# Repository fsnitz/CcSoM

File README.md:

# CcSoM

## Description
CcSoM is a credit card-sized System on Module built around the GateMate FPGA from Cologne Chip. It is designed to accommodate the CCGM1A1 and CCGM1A2 FPGAs with all their features. 
This repository contains all the necessary design files to fabricate and further develop the SoM itself or an application specific baseboard for it. 
A simple IO tester and programmer baseboard can be found in the [Baseboards](Baseboards) folder.
The [Library](Library) folder contains a symbol and footprint to simplify the process of creating a new baseboard. 
Each board folder includes a PDF version of the board and schematics, as well as an interactive HTML BOM.

## Features: 
  - Choose the IO-Bank supply voltage for each IO-Bank freely within the capability of the GateMate FPGA (default 2.5V).
  - All IOs are routed to the SODIMM-connector and can be accessed either as single-ended signal or as differential pair with its designated partner IO.
  - Configuration of the FPGA is possible over JTAG or the on-board QSPI-Flash.

## Manufacturing notes
- The SoM is designed for JLCPCBs "JLC0610H-3313" layer stack and with vias in pads. If a different manufacturer is chosen, it is advisable to either reroute all differential lines or to find a manufacturer where the layer stack can be specified.
- Most of the resistors and capacitors have a 0201 footprint, which may complicate the manufacturing process. 

## Author
Felix Sebastian Nitz

## Acknowledgment
A special thanks to Cologne chip and its employees for their feedback on the design and FPGA samples.

## License
This project falls under the open hardware licence agreement.

## Project status
- SoM revision 1.0 is currently tested with the CCGM1A1 FPGA. Beginning of 2025 an evaluation of its capabilities with an CCGM1A2 will follow.
- A version of the SoM with a 0402 footprint can be found under its designated Tag [0402 Version](https://github.com/fsnitz/CcSoM/tree/VersionWith0402Components).

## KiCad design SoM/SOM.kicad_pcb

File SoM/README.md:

# CcSoM

## Description
CcSoM is a credit card-sized System on Module built around the GateMate FPGA from Cologne Chip. It is designed to accommodate the CCGM1A1 and CCGM1A2 FPGAs with all their features. 
This repository contains all the necessary design files to fabricate and further develop the SoM itself or an application specific baseboard for it. 
A simple IO tester and programmer baseboard can be found in the Baseboard subfolder.
The Library folder contains a symbol and footprint to simplify the process of creating a new baseboard. 
Each board folder includes a PDF version of the board and schematics, as well as an interactive HTML BOM.

## Features: 
  - Choose the IO-Bank supply voltage for each IO-Bank freely within the capability of the GateMate FPGA (default 2.5V).
  - All IOs are routed to the SODIM-connector and can be accessed either as single-ended signal or as differential pair with its designated partner IO.
  - Configuration of the FPGA is possible over JTAG or the on-board QSPI-Flash.

## Manufacturing notes
- The SoM is designed for JLCPCBs "JLC0610H-3313" layer stack and with vias in pads. If a different manufacturer is chosen, it is advisable to either reroute all differential lines or to find a manufacturer where the layer stack can be specified.
- Most of the Resistors and Capacitors have a 0201 footprint, which may complicate the manufacturing process. 

## Author
Felix Sebastian Nitz

## Acknowledgment
A special thanks to Cologne chip and its employees for their feedback on the design and FPGA samples.

## License
This project falls under the open hardware licence agreement.

## Project status
- SoM revision 1.0 is currently tested with the CCGM1A1 FPGA. Beginning of 2025 an evaluation of its capabilities with an CCGM1A2 will follow.
- A version of the SoM with a 0402 footprint may be available, depending on demand.

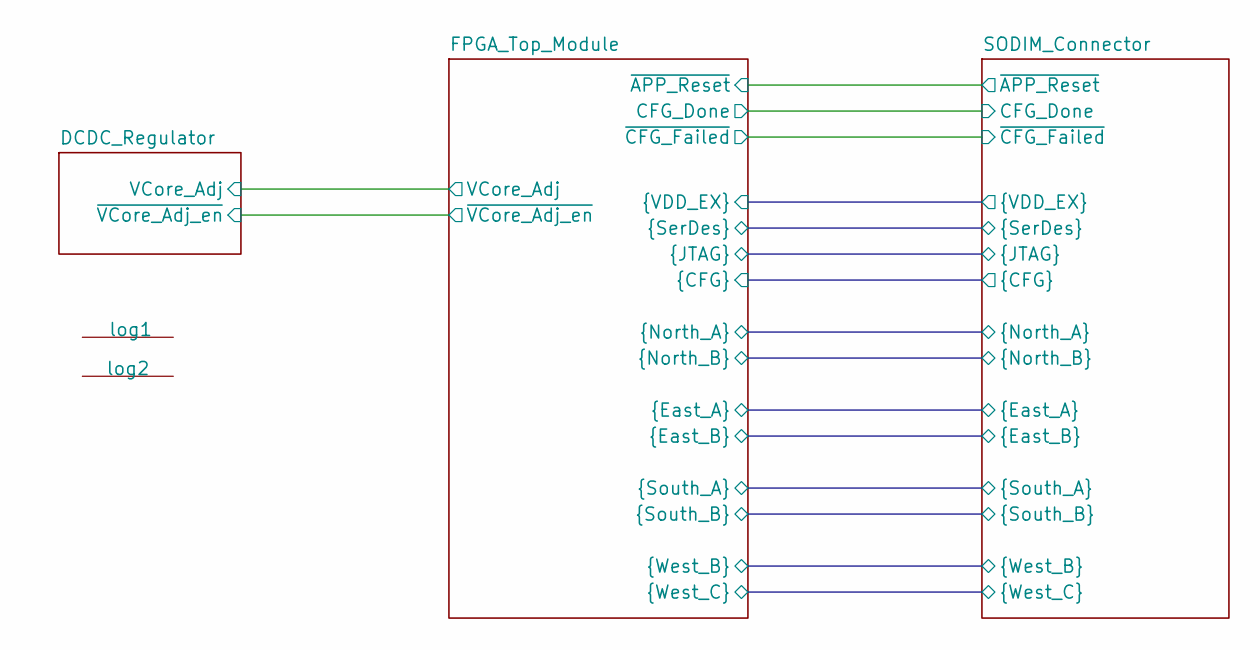
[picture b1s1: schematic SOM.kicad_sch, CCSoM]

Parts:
log1: PinguinLogo
log2: OpenHardwareLogo

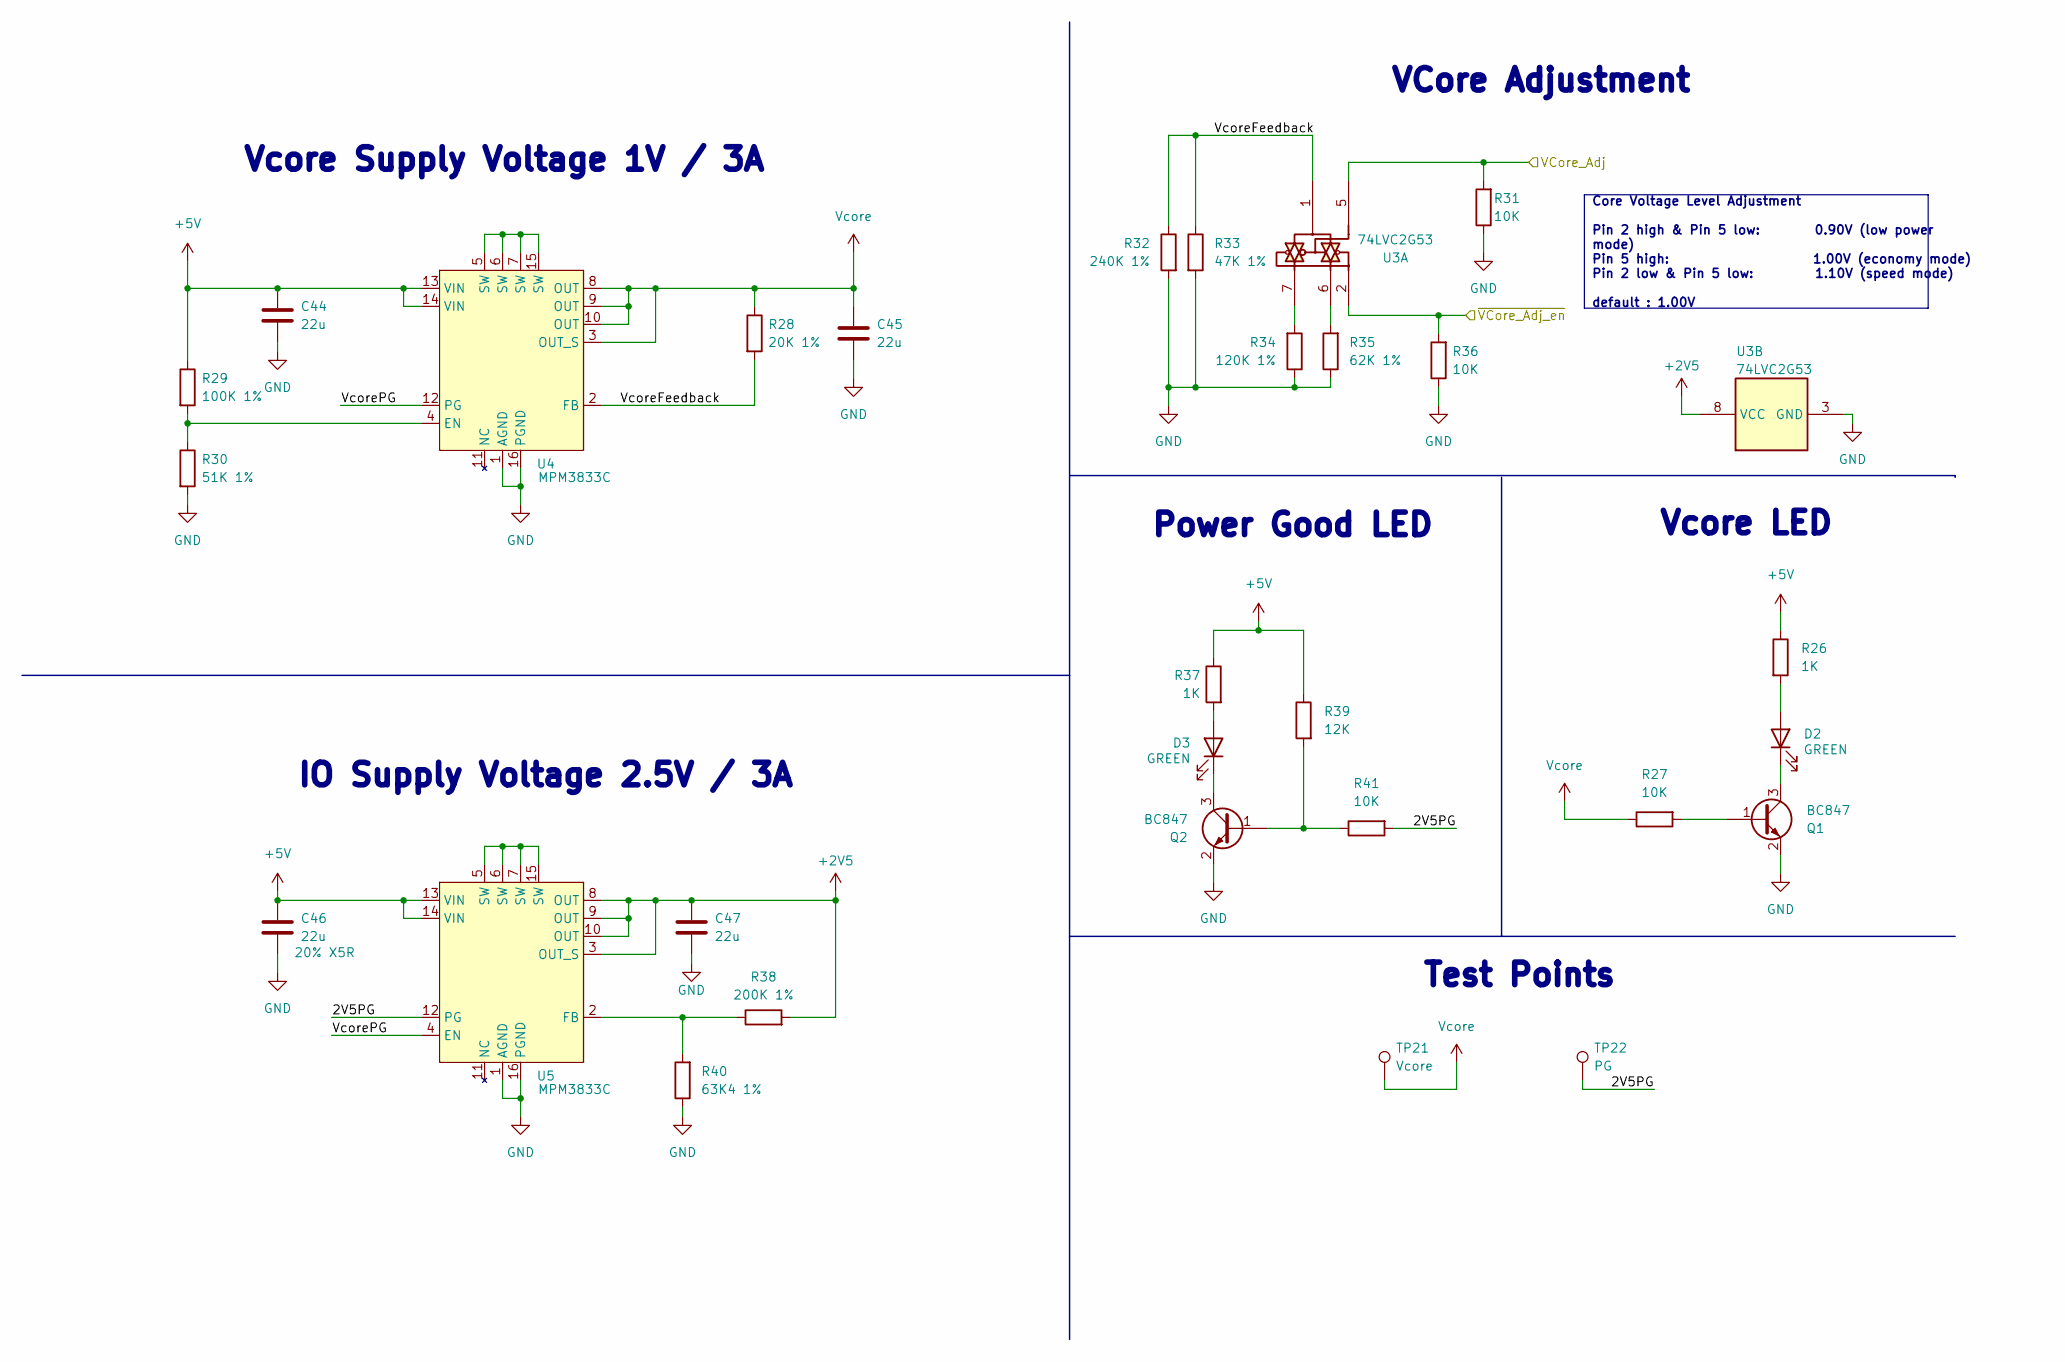
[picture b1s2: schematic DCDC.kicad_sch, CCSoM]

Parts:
C44, C45, C46, C47: 22u; C_0603_1608Metric; Mouser Part Number GRM188C61C226ME01W
D2, D3: GREEN; LED_0603_1608Metric; Mouser Part Number 150060VS75000
Q1, Q2: BC847; SOT-23; Mouser Part Number BC847C-C
R26, R37: 1K; R_0402_1005Metric; Mouser Part Number MCS04020C1001FE000
R27, R31, R36, R41: 10K; R_0402_1005Metric; Mouser Part Number MCS0402MC1002FE000
R28: 20K 1%; R_0402_1005Metric; Mouser Part Number CRCW040220K0FKED
R29: 100K 1%; R_0402_1005Metric; Mouser Part Number MCS04020C1003FE000
R30: 51K 1%; R_0402_1005Metric; Mouser Part Number CRCW040251K0FKEDC
R32: 240K 1%; R_0402_1005Metric; Mouser Part Number MCS04020C2403FE000
R33: 47K 1%; R_0402_1005Metric; Mouser Part Number CRCW040247K0FKED
R34: 120K 1%; R_0402_1005Metric; Mouser Part Number MCS04020C1203FE000
R35: 62K 1%; R_0402_1005Metric; Mouser Part Number CRCW040262K0FKED
R38: 200K 1%; R_0402_1005Metric; Mouser Part Number CRCW0402200KFKEDC
R39: 12K; R_0402_1005Metric; Mouser Part Number MCS04020C1202FE000
R40: 63K4 1%; R_0402_1005Metric; Mouser Part Number CRCW040263K4FKED
TP21: Vcore; TestPoint_Pad_D1.0mm
TP22: PG; TestPoint_Pad_D1.0mm
U3: 74LVC2G53; DCU8; Mouser Part Number SN74LVC2G53DCUR
U4, U5: MPM3833C; QFN18; Mouser Part Number MPM3833CGRH-Z

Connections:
+2V5: C47.1, R38.2, U3.8 (VCC), U5.3 (OUT_S), U5.8 (OUT), U5.9 (OUT), U5.10 (OUT), U5.20 (OUT); also elsewhere on the board
+5V: C44.1, C46.1, R26.1, R29.1, R37.1, R39.1, U4.13 (VIN), U4.14 (VIN), U5.13 (VIN), U5.14 (VIN); also elsewhere on the board
/DCDC_Regulator/2V5PG: R41.2, TP22.1, U5.12 (PG)
/DCDC_Regulator/VcoreFeedback: R28.2, R32.1, R33.1, U3.1, U4.2 (FB)
/DCDC_Regulator/VcorePG: U4.12 (PG), U5.4 (EN)
/FPGA_Top_Module/VcAdj: R31.2, U3.5; also elsewhere on the board
/FPGA_Top_Module/~VcAen: R36.2, U3.2; also elsewhere on the board
GND: C44.2, C45.2, C46.2, C47.2, Q1.2 (E), Q2.2 (E), R30.2, R31.1, R32.2, R33.2, R34.1, R35.1, R36.1, R40.1, U3.3 (GND), U3.4 (GND), U4.1 (AGND), U4.16 (PGND), U5.1 (AGND), U5.16 (PGND); also elsewhere on the board
unnamed: D2.2 (A), R26.2
unnamed: D2.1 (K), Q1.3 (C)
unnamed: D3.2 (A), R37.2
unnamed: D3.1 (K), Q2.3 (C)
unnamed: Q1.1 (B), R27.2
unnamed: Q2.1 (B), R39.2, R41.1
unnamed: R34.2, U3.7
unnamed: R35.2, U3.6
unnamed: R29.2, R30.1, U4.4 (EN)
unnamed: U4.5 (SW), U4.6 (SW), U4.7 (SW), U4.15 (SW), U4.19 (SW)
unnamed: R38.1, R40.2, U5.2 (FB)
unnamed: U5.5 (SW), U5.6 (SW), U5.7 (SW), U5.15 (SW), U5.19 (SW)
Vcore: C45.1, R27.1, R28.1, TP21.1, U4.3 (OUT_S), U4.8 (OUT), U4.9 (OUT), U4.10 (OUT), U4.20 (OUT); also elsewhere on the board

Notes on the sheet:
Power Good LED
Test Points
Vcore LED
Vcore Supply Voltage 1V / 3A
IO Supply Voltage 2.5V / 3A
VCore Adjustment
Core Voltage Level Adjustment Pin 2 high & Pin 5 low: 0.90V (low power mode) Pin 5 high: 1.00V (economy mode) Pin 2 low & Pin 5 low: 1.10V (speed mode) default : 1.00V

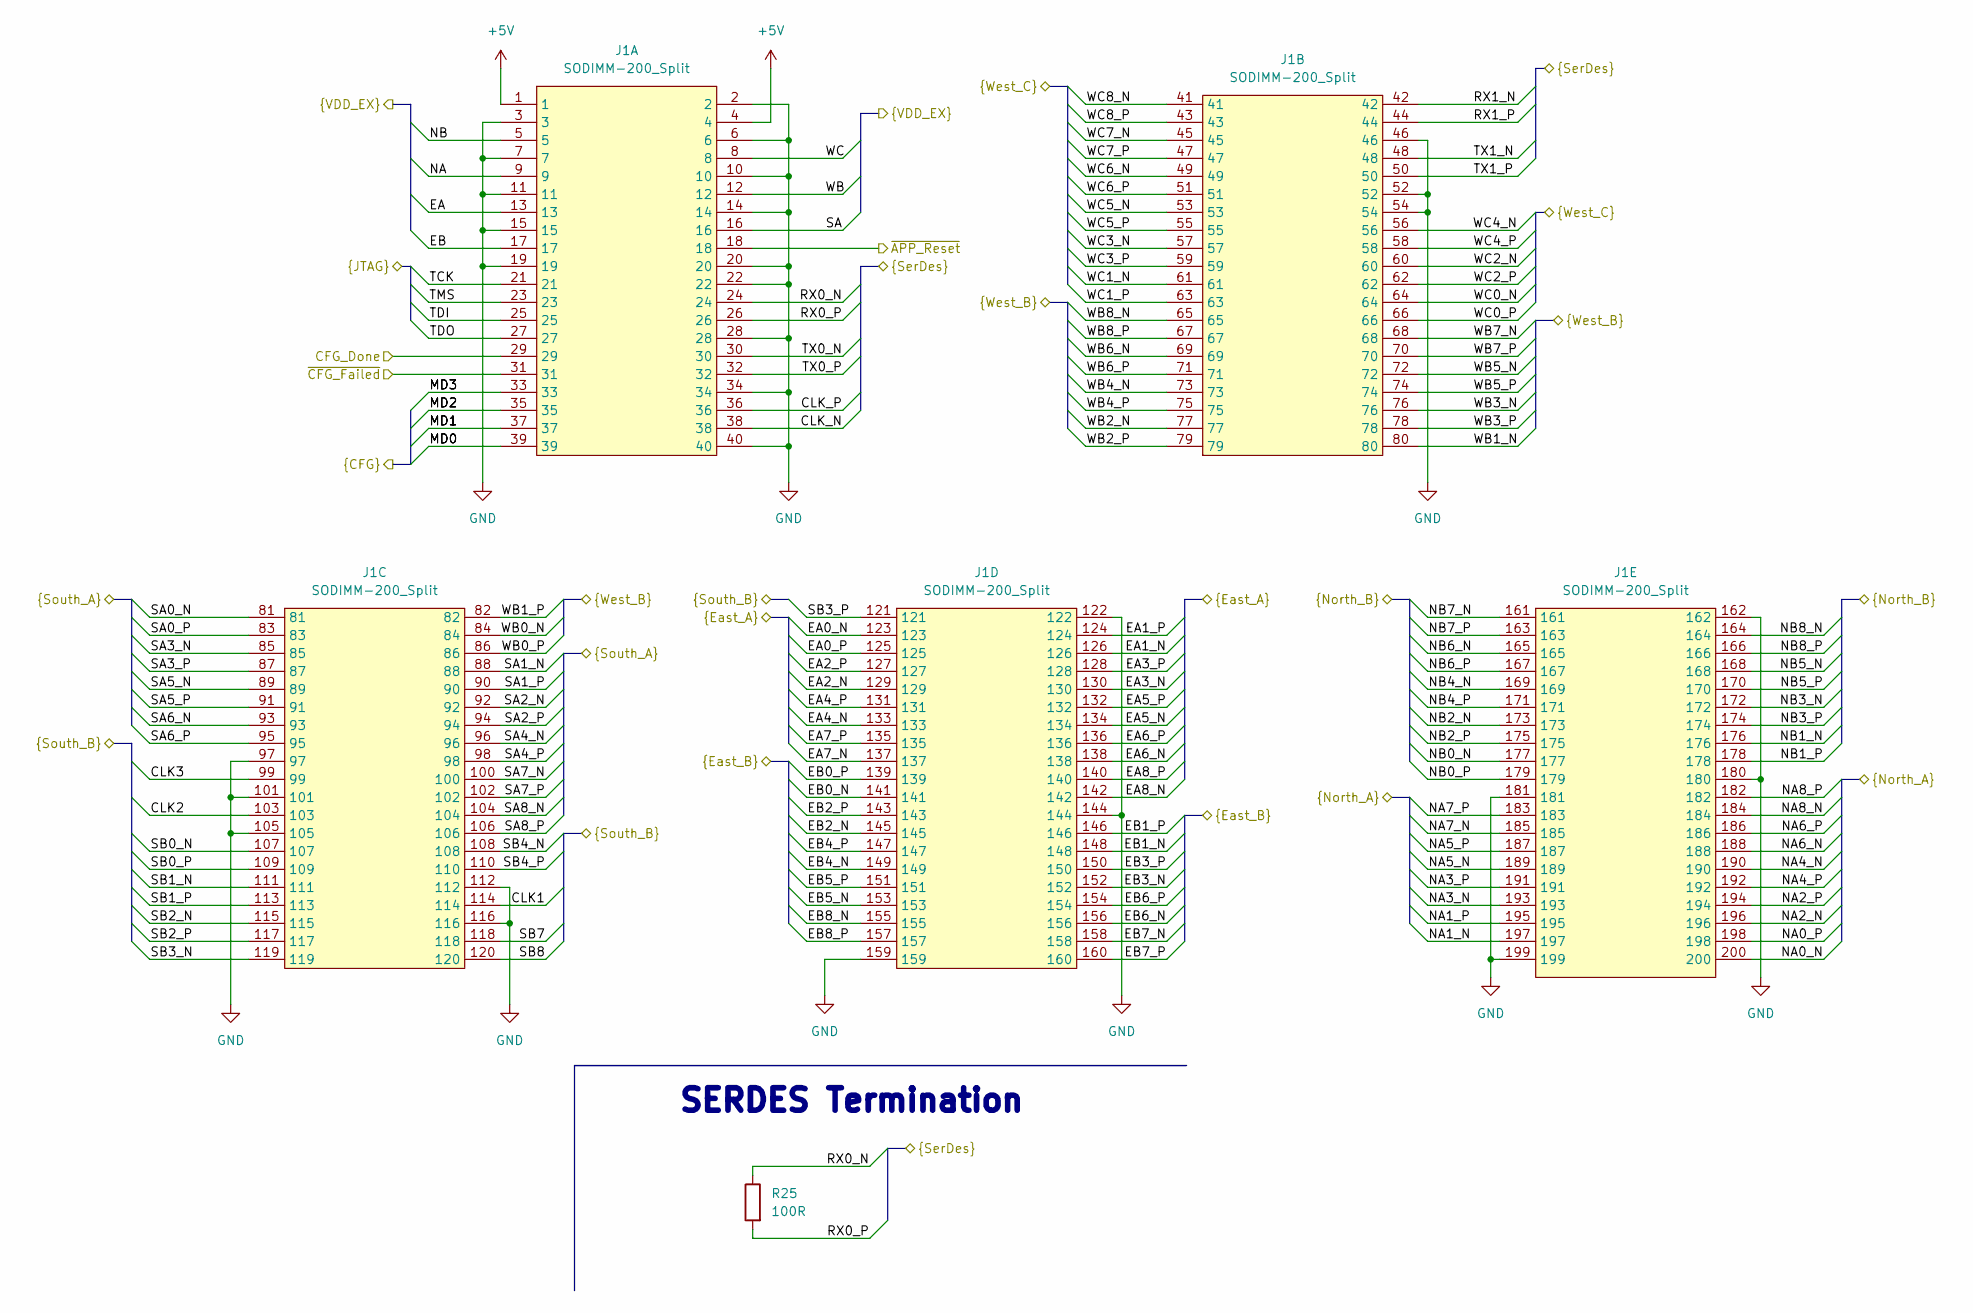
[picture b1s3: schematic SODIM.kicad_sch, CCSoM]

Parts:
J1: SODIMM-200_Split; SODIMM-200_2.5V_Card_edge
R25: 100R; R_0402_1005Metric; Mouser Part Number MCS04020C1000FE000

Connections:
+5V: J1.1, J1.4; also elsewhere on the board
/FPGA_Top_Module/CFG_Done: J1.29; also elsewhere on the board
/FPGA_Top_Module/CLK1: J1.114; also elsewhere on the board
/FPGA_Top_Module/CLK2: J1.103; also elsewhere on the board
/FPGA_Top_Module/CLK3: J1.99; also elsewhere on the board
/FPGA_Top_Module/CLK_N: J1.38; also elsewhere on the board
/FPGA_Top_Module/CLK_P: J1.36; also elsewhere on the board
/FPGA_Top_Module/EA: J1.13; also elsewhere on the board
/FPGA_Top_Module/EA0_N: J1.123; also elsewhere on the board
/FPGA_Top_Module/EA0_P: J1.125; also elsewhere on the board
/FPGA_Top_Module/EA1_N: J1.126; also elsewhere on the board
/FPGA_Top_Module/EA1_P: J1.124; also elsewhere on the board
/FPGA_Top_Module/EA2_N: J1.129; also elsewhere on the board
/FPGA_Top_Module/EA2_P: J1.127; also elsewhere on the board
/FPGA_Top_Module/EA3_N: J1.130; also elsewhere on the board
/FPGA_Top_Module/EA3_P: J1.128; also elsewhere on the board
/FPGA_Top_Module/EA4_N: J1.133; also elsewhere on the board
/FPGA_Top_Module/EA4_P: J1.131; also elsewhere on the board
/FPGA_Top_Module/EA5_N: J1.134; also elsewhere on the board
/FPGA_Top_Module/EA5_P: J1.132; also elsewhere on the board
/FPGA_Top_Module/EA6_N: J1.138; also elsewhere on the board
/FPGA_Top_Module/EA6_P: J1.136; also elsewhere on the board
/FPGA_Top_Module/EA7_N: J1.137; also elsewhere on the board
/FPGA_Top_Module/EA7_P: J1.135; also elsewhere on the board
/FPGA_Top_Module/EA8_N: J1.142; also elsewhere on the board
/FPGA_Top_Module/EA8_P: J1.140; also elsewhere on the board
/FPGA_Top_Module/EB: J1.17; also elsewhere on the board
/FPGA_Top_Module/EB0_N: J1.141; also elsewhere on the board
/FPGA_Top_Module/EB0_P: J1.139; also elsewhere on the board
/FPGA_Top_Module/EB1_N: J1.148; also elsewhere on the board
/FPGA_Top_Module/EB1_P: J1.146; also elsewhere on the board
/FPGA_Top_Module/EB2_N: J1.145; also elsewhere on the board
/FPGA_Top_Module/EB2_P: J1.143; also elsewhere on the board
/FPGA_Top_Module/EB3_N: J1.152; also elsewhere on the board
/FPGA_Top_Module/EB3_P: J1.150; also elsewhere on the board
/FPGA_Top_Module/EB4_N: J1.149; also elsewhere on the board
/FPGA_Top_Module/EB4_P: J1.147; also elsewhere on the board
/FPGA_Top_Module/EB5_N: J1.153; also elsewhere on the board
/FPGA_Top_Module/EB5_P: J1.151; also elsewhere on the board
/FPGA_Top_Module/EB6_N: J1.156; also elsewhere on the board
/FPGA_Top_Module/EB6_P: J1.154; also elsewhere on the board
/FPGA_Top_Module/EB7_N: J1.158; also elsewhere on the board
/FPGA_Top_Module/EB7_P: J1.160; also elsewhere on the board
/FPGA_Top_Module/EB8_N: J1.155; also elsewhere on the board
/FPGA_Top_Module/EB8_P: J1.157; also elsewhere on the board
/FPGA_Top_Module/MD0: J1.39; also elsewhere on the board
/FPGA_Top_Module/MD1: J1.37; also elsewhere on the board
/FPGA_Top_Module/MD2: J1.35; also elsewhere on the board
/FPGA_Top_Module/MD3: J1.33; also elsewhere on the board
/FPGA_Top_Module/NA: J1.9; also elsewhere on the board
/FPGA_Top_Module/NA0_N: J1.200; also elsewhere on the board
/FPGA_Top_Module/NA0_P: J1.198; also elsewhere on the board
/FPGA_Top_Module/NA1_N: J1.197; also elsewhere on the board
/FPGA_Top_Module/NA1_P: J1.195; also elsewhere on the board
/FPGA_Top_Module/NA2_N: J1.196; also elsewhere on the board
/FPGA_Top_Module/NA2_P: J1.194; also elsewhere on the board
/FPGA_Top_Module/NA3_N: J1.193; also elsewhere on the board
/FPGA_Top_Module/NA3_P: J1.191; also elsewhere on the board
/FPGA_Top_Module/NA4_N: J1.190; also elsewhere on the board
/FPGA_Top_Module/NA4_P: J1.192; also elsewhere on the board
/FPGA_Top_Module/NA5_N: J1.189; also elsewhere on the board
/FPGA_Top_Module/NA5_P: J1.187; also elsewhere on the board
/FPGA_Top_Module/NA6_N: J1.188; also elsewhere on the board
/FPGA_Top_Module/NA6_P: J1.186; also elsewhere on the board
/FPGA_Top_Module/NA7_N: J1.185; also elsewhere on the board
/FPGA_Top_Module/NA7_P: J1.183; also elsewhere on the board
/FPGA_Top_Module/NA8_N: J1.184; also elsewhere on the board
/FPGA_Top_Module/NA8_P: J1.182; also elsewhere on the board
/FPGA_Top_Module/NB: J1.5; also elsewhere on the board
/FPGA_Top_Module/NB0_N: J1.177; also elsewhere on the board
/FPGA_Top_Module/NB0_P: J1.179; also elsewhere on the board
/FPGA_Top_Module/NB1_N: J1.176; also elsewhere on the board
/FPGA_Top_Module/NB1_P: J1.178; also elsewhere on the board
/FPGA_Top_Module/NB2_N: J1.173; also elsewhere on the board
/FPGA_Top_Module/NB2_P: J1.175; also elsewhere on the board
/FPGA_Top_Module/NB3_N: J1.172; also elsewhere on the board
/FPGA_Top_Module/NB3_P: J1.174; also elsewhere on the board
/FPGA_Top_Module/NB4_N: J1.169; also elsewhere on the board
/FPGA_Top_Module/NB4_P: J1.171; also elsewhere on the board
/FPGA_Top_Module/NB5_N: J1.168; also elsewhere on the board
/FPGA_Top_Module/NB5_P: J1.170; also elsewhere on the board
/FPGA_Top_Module/NB6_N: J1.165; also elsewhere on the board
/FPGA_Top_Module/NB6_P: J1.167; also elsewhere on the board
/FPGA_Top_Module/NB7_N: J1.161; also elsewhere on the board
/FPGA_Top_Module/NB7_P: J1.163; also elsewhere on the board
/FPGA_Top_Module/NB8_N: J1.164; also elsewhere on the board
/FPGA_Top_Module/NB8_P: J1.166; also elsewhere on the board
/FPGA_Top_Module/RX0_N: J1.24, R25.1; also elsewhere on the board
/FPGA_Top_Module/RX0_P: J1.26, R25.2; also elsewhere on the board
/FPGA_Top_Module/RX1_N: J1.42; also elsewhere on the board
/FPGA_Top_Module/RX1_P: J1.44; also elsewhere on the board
/FPGA_Top_Module/SA: J1.16; also elsewhere on the board
/FPGA_Top_Module/SA0_N: J1.81; also elsewhere on the board
/FPGA_Top_Module/SA0_P: J1.83; also elsewhere on the board
/FPGA_Top_Module/SA1_N: J1.88; also elsewhere on the board
/FPGA_Top_Module/SA1_P: J1.90; also elsewhere on the board
/FPGA_Top_Module/SA2_N: J1.92; also elsewhere on the board
/FPGA_Top_Module/SA2_P: J1.94; also elsewhere on the board
/FPGA_Top_Module/SA3_N: J1.85; also elsewhere on the board
/FPGA_Top_Module/SA3_P: J1.87; also elsewhere on the board
/FPGA_Top_Module/SA4_N: J1.96; also elsewhere on the board
/FPGA_Top_Module/SA4_P: J1.98; also elsewhere on the board
/FPGA_Top_Module/SA5_N: J1.89; also elsewhere on the board
/FPGA_Top_Module/SA5_P: J1.91; also elsewhere on the board
/FPGA_Top_Module/SA6_N: J1.93; also elsewhere on the board
/FPGA_Top_Module/SA6_P: J1.95; also elsewhere on the board
/FPGA_Top_Module/SA7_N: J1.100; also elsewhere on the board
/FPGA_Top_Module/SA7_P: J1.102; also elsewhere on the board
/FPGA_Top_Module/SA8_N: J1.104; also elsewhere on the board
/FPGA_Top_Module/SA8_P: J1.106; also elsewhere on the board
/FPGA_Top_Module/SB0_N: J1.107; also elsewhere on the board
/FPGA_Top_Module/SB0_P: J1.109; also elsewhere on the board
/FPGA_Top_Module/SB1_N: J1.111; also elsewhere on the board
/FPGA_Top_Module/SB1_P: J1.113; also elsewhere on the board
/FPGA_Top_Module/SB2_N: J1.115; also elsewhere on the board
/FPGA_Top_Module/SB2_P: J1.117; also elsewhere on the board
/FPGA_Top_Module/SB3_N: J1.119; also elsewhere on the board
/FPGA_Top_Module/SB3_P: J1.121; also elsewhere on the board
/FPGA_Top_Module/SB4_N: J1.108; also elsewhere on the board
/FPGA_Top_Module/SB4_P: J1.110; also elsewhere on the board
/FPGA_Top_Module/SB7: J1.118; also elsewhere on the board
/FPGA_Top_Module/SB8: J1.120; also elsewhere on the board
/FPGA_Top_Module/TCK: J1.21; also elsewhere on the board
/FPGA_Top_Module/TDI: J1.25; also elsewhere on the board
/FPGA_Top_Module/TDO: J1.27; also elsewhere on the board
/FPGA_Top_Module/TMS: J1.23; also elsewhere on the board
/FPGA_Top_Module/TX0_N: J1.30; also elsewhere on the board
/FPGA_Top_Module/TX0_P: J1.32; also elsewhere on the board
/FPGA_Top_Module/TX1_N: J1.48; also elsewhere on the board
/FPGA_Top_Module/TX1_P: J1.50; also elsewhere on the board
/FPGA_Top_Module/WB: J1.12; also elsewhere on the board
/FPGA_Top_Module/WB0_N: J1.84; also elsewhere on the board
/FPGA_Top_Module/WB0_P: J1.86; also elsewhere on the board
/FPGA_Top_Module/WB1_N: J1.80; also elsewhere on the board
/FPGA_Top_Module/WB1_P: J1.82; also elsewhere on the board
/FPGA_Top_Module/WB2_N: J1.77; also elsewhere on the board
/FPGA_Top_Module/WB2_P: J1.79; also elsewhere on the board
/FPGA_Top_Module/WB3_N: J1.76; also elsewhere on the board
/FPGA_Top_Module/WB3_P: J1.78; also elsewhere on the board
/FPGA_Top_Module/WB4_N: J1.73; also elsewhere on the board
/FPGA_Top_Module/WB4_P: J1.75; also elsewhere on the board
/FPGA_Top_Module/WB5_N: J1.72; also elsewhere on the board
/FPGA_Top_Module/WB5_P: J1.74; also elsewhere on the board
/FPGA_Top_Module/WB6_N: J1.69; also elsewhere on the board
/FPGA_Top_Module/WB6_P: J1.71; also elsewhere on the board
/FPGA_Top_Module/WB7_N: J1.68; also elsewhere on the board
/FPGA_Top_Module/WB7_P: J1.70; also elsewhere on the board
/FPGA_Top_Module/WB8_N: J1.65; also elsewhere on the board
/FPGA_Top_Module/WB8_P: J1.67; also elsewhere on the board
/FPGA_Top_Module/WC: J1.8; also elsewhere on the board
/FPGA_Top_Module/WC0_N: J1.64; also elsewhere on the board
/FPGA_Top_Module/WC0_P: J1.66; also elsewhere on the board
/FPGA_Top_Module/WC1_N: J1.61; also elsewhere on the board
/FPGA_Top_Module/WC1_P: J1.63; also elsewhere on the board
/FPGA_Top_Module/WC2_N: J1.60; also elsewhere on the board
/FPGA_Top_Module/WC2_P: J1.62; also elsewhere on the board
/FPGA_Top_Module/WC3_N: J1.57; also elsewhere on the board
/FPGA_Top_Module/WC3_P: J1.59; also elsewhere on the board
/FPGA_Top_Module/WC4_N: J1.56; also elsewhere on the board
/FPGA_Top_Module/WC4_P: J1.58; also elsewhere on the board
/FPGA_Top_Module/WC5_N: J1.53; also elsewhere on the board
/FPGA_Top_Module/WC5_P: J1.55; also elsewhere on the board
/FPGA_Top_Module/WC6_N: J1.49; also elsewhere on the board
/FPGA_Top_Module/WC6_P: J1.51; also elsewhere on the board
/FPGA_Top_Module/WC7_N: J1.45; also elsewhere on the board
/FPGA_Top_Module/WC7_P: J1.47; also elsewhere on the board
/FPGA_Top_Module/WC8_N: J1.41; also elsewhere on the board
/FPGA_Top_Module/WC8_P: J1.43; also elsewhere on the board
/FPGA_Top_Module/~CFG_Failed: J1.31; also elsewhere on the board
/FPGA_Top_Module/~Rst: J1.18; also elsewhere on the board
GND: J1.2, J1.3, J1.6, J1.7, J1.10, J1.11, J1.14, J1.15, J1.19, J1.20, J1.22, J1.28, J1.34, J1.40, J1.46, J1.52, J1.54, J1.97, J1.101, J1.105, J1.112, J1.116, J1.122, J1.144, J1.159, J1.162, J1.180, J1.181, J1.199; also elsewhere on the board

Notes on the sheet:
SERDES Termination

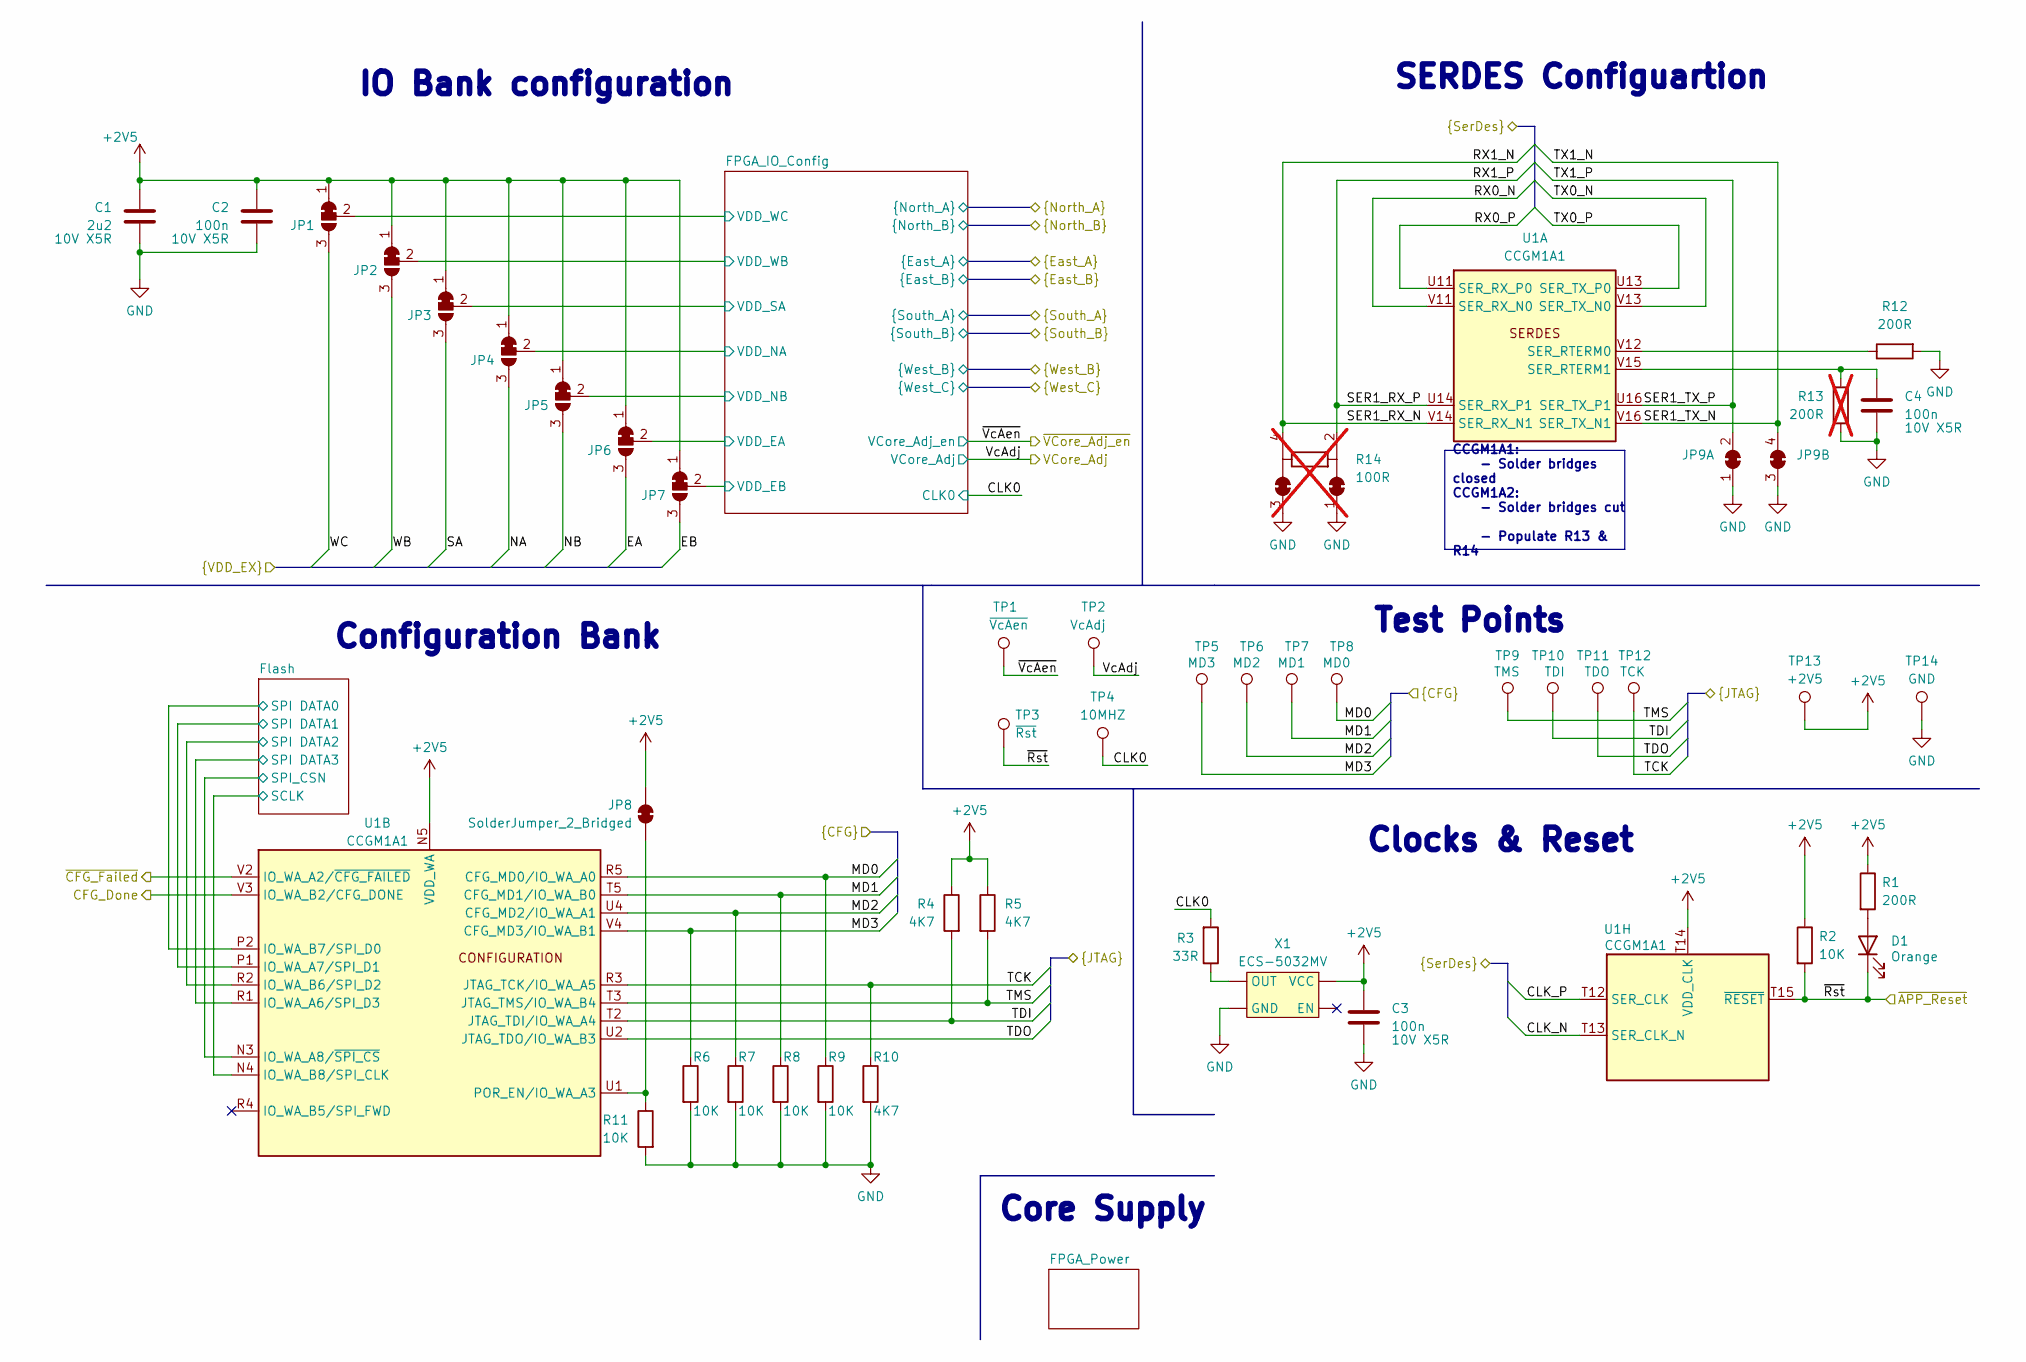
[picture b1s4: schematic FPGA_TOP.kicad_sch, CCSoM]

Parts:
C1: 2u2; C_0402_1005Metric; Voltage/Precision 10V X5R; Mouser Part Number GRM155Z71A225KE44D
C2, C3, C4: 100n; C_0402_1005Metric; Voltage/Precision 10V X5R; Mouser Part Number GRM155R71C104KA88J
D1: Orange; LED_0603_1608Metric; Mouser Part Number APT1608SECK-AMT
JP1, JP2, JP3, JP4, JP5, JP6, JP7: SolderJumper_3_Bridged12; SolderBridge3Pin
JP8: SolderJumper_2_Bridged; Solderbridge_closed
JP9: Diff_pair_solderbridge_closed
R1, R12: 200R; R_0402_1005Metric; Mouser Part Number MCS04020C2000FE000
R2, R6, R7, R8, R9, R11: 10K; R_0402_1005Metric; Mouser Part Number MCS0402MC1002FE000
R3: 33R; R_0402_1005Metric; Mouser Part Number MCS04020C3309FE000
R4, R5, R10: 4K7; R_0402_1005Metric; Mouser Part Number CRCW04024K70FKED
R13: 200R; R_0402_1005Metric; Mouser Part Number 71-CRCW0201-200; not fitted
R14: 100R; Diff_pair_solderbridge_closed; not fitted
TP1: ~{VcAen}; TestPoint_Pad_D1.0mm
TP2: VcAdj; TestPoint_Pad_D1.0mm
TP3: ~{Rst}; TestPoint_Pad_D1.0mm
TP4: 10MHZ; TestPoint_Pad_D1.0mm
TP5: MD3; TestPoint_Pad_D1.0mm
TP6: MD2; TestPoint_Pad_D1.0mm
TP7: MD1; TestPoint_Pad_D1.0mm
TP8: MD0; TestPoint_Pad_D1.0mm
TP9: TMS; TestPoint_Pad_D1.0mm
TP10: TDI; TestPoint_Pad_D1.0mm
TP11: TDO; TestPoint_Pad_D1.0mm
TP12: TCK; TestPoint_Pad_D1.0mm
TP13: +2V5; TestPoint_Pad_D1.0mm
TP14: GND; TestPoint_Pad_D1.0mm
U1: CCGM1A1; BGA-324_15.0x15.0mm_Layout18x18_P0.8mm_Ball0.45mm_Pad0.4mm_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; Mouser Part Number CCGM1A1-BGA324
X1: ECS-5032MV; 5x3.2_Oscillator; Mouser Part Number ECS-5032MV-100-BN-TR

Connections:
+2V5: C1.1, C2.1, C3.1, JP1.1 (A), JP2.1 (A), JP3.1 (A), JP4.1 (A), JP5.1 (A), JP6.1 (A), JP7.1 (A), JP8.2 (B), R1.1, R2.1, R4.1, R5.1, TP13.1, U1.N5 (VDD_WA), U1.P3 (VDD_WA), U1.P5 (VDD_WA), U1.T1 (VDD_WA), U1.T14 (VDD_CLK), U1.U3 (VDD_WA), X1.4 (VCC); also elsewhere on the board
/FPGA_Top_Module/CFG_Done: U1.V3 (IO_WA_B2/CFG_DONE); also elsewhere on the board
/FPGA_Top_Module/CLK0: R3.2, TP4.1; also elsewhere on the board
/FPGA_Top_Module/CLK_N: U1.T13 (SER_CLK_N); also elsewhere on the board
/FPGA_Top_Module/CLK_P: U1.T12 (SER_CLK); also elsewhere on the board
/FPGA_Top_Module/EA: JP6.3 (B); also elsewhere on the board
/FPGA_Top_Module/EB: JP7.3 (B); also elsewhere on the board
/FPGA_Top_Module/FPGA_IO_Config/VDD_EA: JP6.2 (C); also elsewhere on the board
/FPGA_Top_Module/FPGA_IO_Config/VDD_EB: JP7.2 (C); also elsewhere on the board
/FPGA_Top_Module/FPGA_IO_Config/VDD_NA: JP4.2 (C); also elsewhere on the board
/FPGA_Top_Module/FPGA_IO_Config/VDD_NB: JP5.2 (C); also elsewhere on the board
/FPGA_Top_Module/FPGA_IO_Config/VDD_SA: JP3.2 (C); also elsewhere on the board
/FPGA_Top_Module/FPGA_IO_Config/VDD_WB: JP2.2 (C); also elsewhere on the board
/FPGA_Top_Module/FPGA_IO_Config/VDD_WC: JP1.2 (C); also elsewhere on the board
/FPGA_Top_Module/Flash/SCLK: U1.N4 (IO_WA_B8/SPI_CLK); also elsewhere on the board
/FPGA_Top_Module/Flash/SPI DATA0: U1.P2 (IO_WA_B7/SPI_D0); also elsewhere on the board
/FPGA_Top_Module/Flash/SPI DATA1: U1.P1 (IO_WA_A7/SPI_D1); also elsewhere on the board
/FPGA_Top_Module/Flash/SPI DATA2: U1.R2 (IO_WA_B6/SPI_D2); also elsewhere on the board
/FPGA_Top_Module/Flash/SPI DATA3: U1.R1 (IO_WA_A6/SPI_D3); also elsewhere on the board
/FPGA_Top_Module/Flash/SPI_CSN: U1.N3 (IO_WA_A8/~SPI_CS); also elsewhere on the board
/FPGA_Top_Module/MD0: R9.1, TP8.1, U1.R5 (CFG_MD0/IO_WA_A0); also elsewhere on the board
/FPGA_Top_Module/MD1: R8.1, TP7.1, U1.T5 (CFG_MD1/IO_WA_B0); also elsewhere on the board
/FPGA_Top_Module/MD2: R7.1, TP6.1, U1.U4 (CFG_MD2/IO_WA_A1); also elsewhere on the board
/FPGA_Top_Module/MD3: R6.1, TP5.1, U1.V4 (CFG_MD3/IO_WA_B1); also elsewhere on the board
/FPGA_Top_Module/NA: JP4.3 (B); also elsewhere on the board
/FPGA_Top_Module/NB: JP5.3 (B); also elsewhere on the board
/FPGA_Top_Module/RX0_N: U1.V11 (SER_RX_N0); also elsewhere on the board
/FPGA_Top_Module/RX0_P: U1.U11 (SER_RX_P0); also elsewhere on the board
/FPGA_Top_Module/RX1_N: R14.4, U1.V14 (SER_RX_N1); also elsewhere on the board
/FPGA_Top_Module/RX1_P: R14.2, U1.U14 (SER_RX_P1); also elsewhere on the board
/FPGA_Top_Module/SA: JP3.3 (B); also elsewhere on the board
/FPGA_Top_Module/TCK: R10.1, TP12.1, U1.R3 (JTAG_TCK/IO_WA_A5); also elsewhere on the board
/FPGA_Top_Module/TDI: R4.2, TP10.1, U1.T2 (JTAG_TDI/IO_WA_A4); also elsewhere on the board
/FPGA_Top_Module/TDO: TP11.1, U1.U2 (JTAG_TDO/IO_WA_B3); also elsewhere on the board
/FPGA_Top_Module/TMS: R5.2, TP9.1, U1.T3 (JTAG_TMS/IO_WA_B4); also elsewhere on the board
/FPGA_Top_Module/TX0_N: U1.V13 (SER_TX_N0); also elsewhere on the board
/FPGA_Top_Module/TX0_P: U1.U13 (SER_TX_P0); also elsewhere on the board
/FPGA_Top_Module/TX1_N: JP9.4 (B), U1.V16 (SER_TX_N1); also elsewhere on the board
/FPGA_Top_Module/TX1_P: JP9.2 (B), U1.U16 (SER_TX_P1); also elsewhere on the board
/FPGA_Top_Module/VcAdj: TP2.1; also elsewhere on the board
/FPGA_Top_Module/WB: JP2.3 (B); also elsewhere on the board
/FPGA_Top_Module/WC: JP1.3 (B); also elsewhere on the board
/FPGA_Top_Module/~CFG_Failed: U1.V2 (IO_WA_A2/~CFG_FAILED); also elsewhere on the board
/FPGA_Top_Module/~Rst: D1.1 (K), R2.2, TP3.1, U1.T15 (~RESET); also elsewhere on the board
/FPGA_Top_Module/~VcAen: TP1.1; also elsewhere on the board
GND: C1.2, C2.2, C3.2, C4.2, JP9.1 (A), JP9.3 (A), R6.2, R7.2, R8.2, R9.2, R10.2, R11.2, R12.2, R13.2, R14.1 (A), R14.3 (A), TP14.1, X1.2 (GND); also elsewhere on the board
unnamed: D1.2 (A), R1.2
unnamed: JP8.1 (A), R11.1, U1.U1 (POR_EN/IO_WA_A3)
unnamed: R12.1, U1.V12 (SER_RTERM0)
unnamed: C4.1, R13.1, U1.V15 (SER_RTERM1)
unnamed: R3.1, X1.3 (OUT)

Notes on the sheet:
Test Points
IO Bank configuration
Core Supply
Clocks & Reset
SERDES Configuartion
Configuration Bank
CCGM1A1: - Solder bridges closed CCGM1A2: - Solder bridges cut - Populate R13 & R14
